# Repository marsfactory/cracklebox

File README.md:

# cracklebox
Diseño de PCB de la clasica crackle box, dandole un toque artistico al diseño. Realizado en el marco del Encuentro Federal de Grafica Tranza 2018.

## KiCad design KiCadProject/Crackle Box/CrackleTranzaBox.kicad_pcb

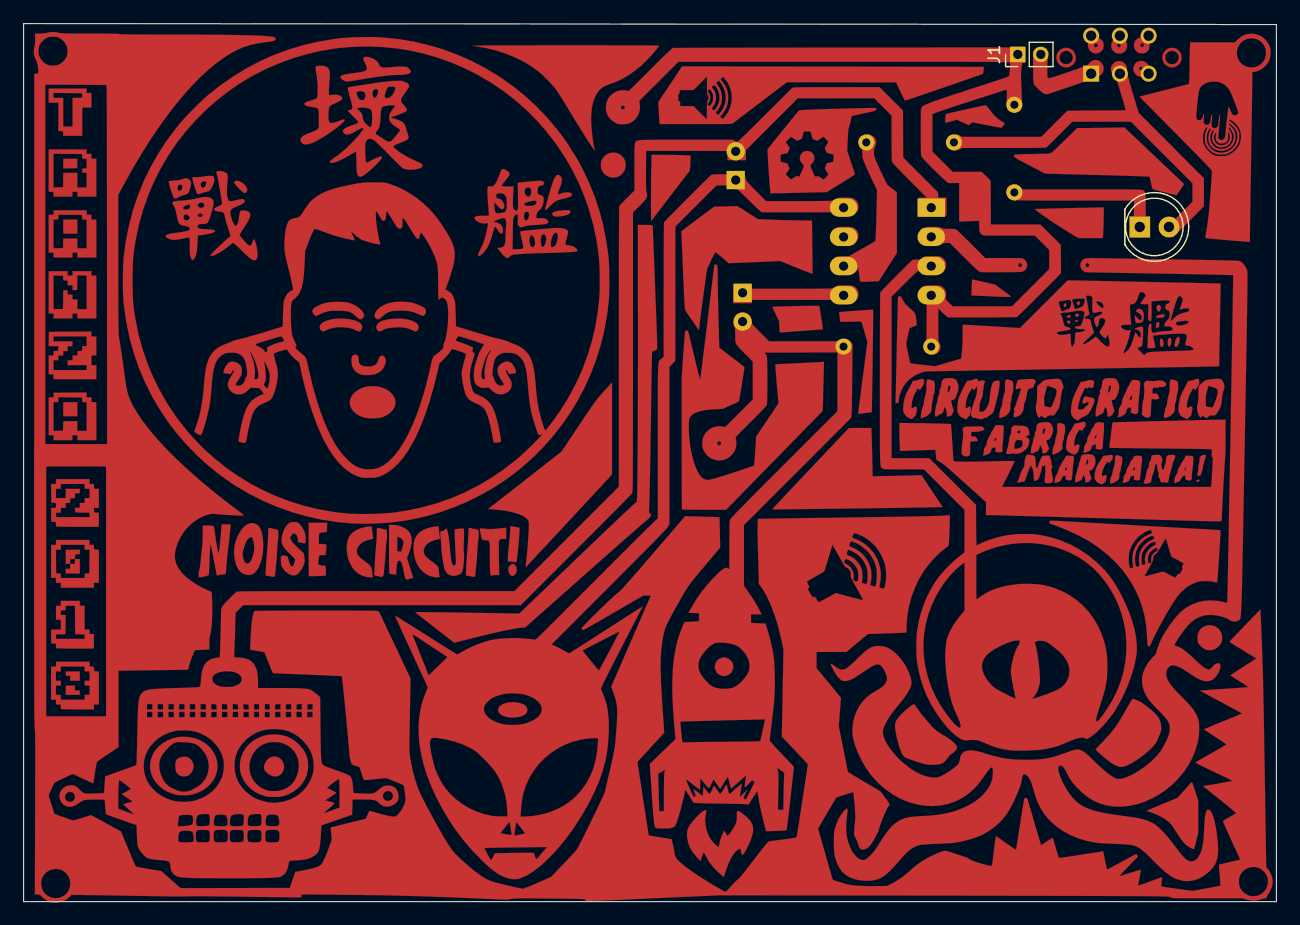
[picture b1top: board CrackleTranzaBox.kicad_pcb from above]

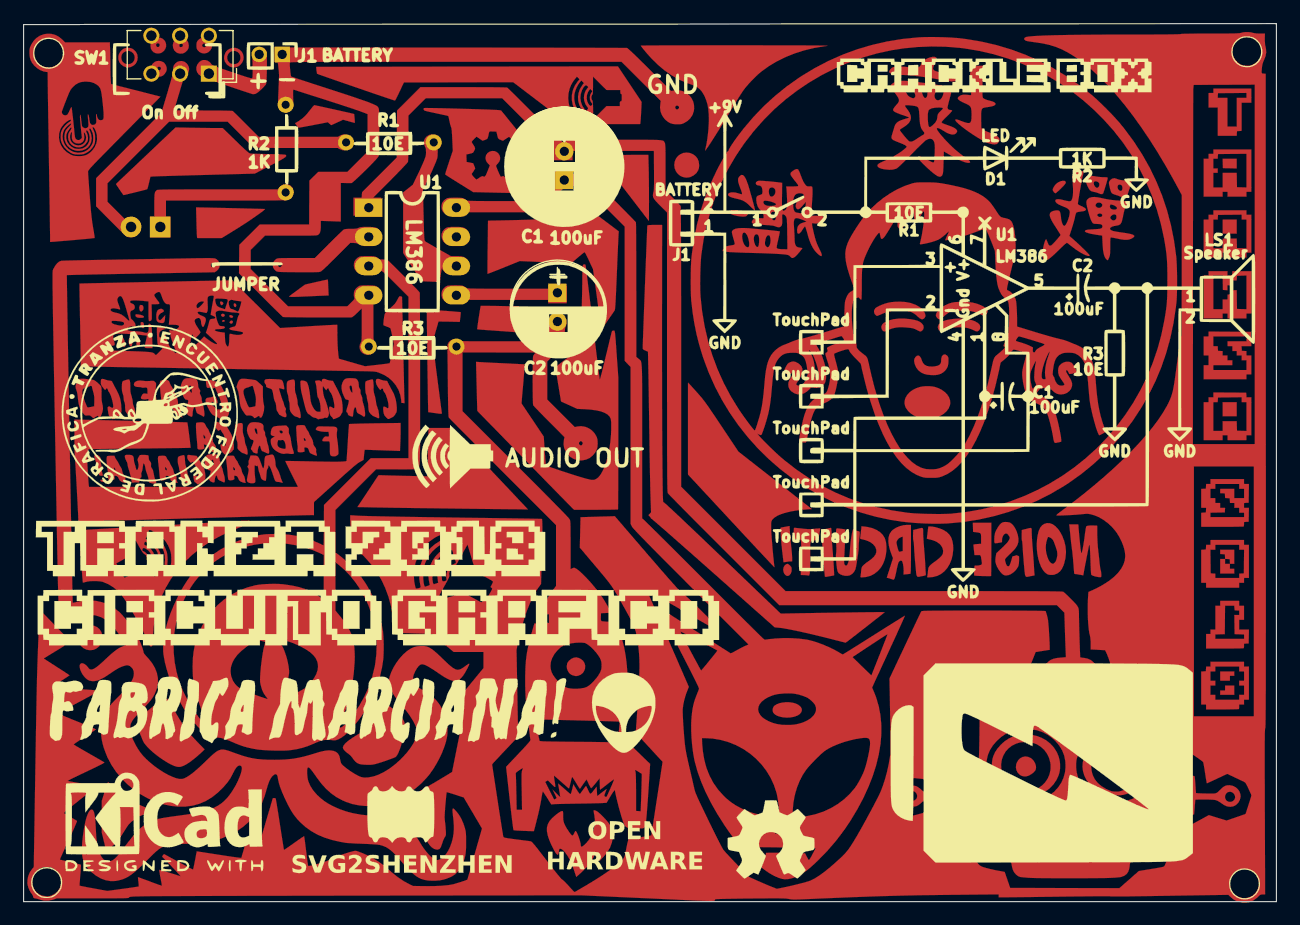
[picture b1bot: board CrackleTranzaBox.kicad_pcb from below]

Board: 2 copper layers, 108.9 x 76.3 mm, 9 parts (7 on the bottom side), 9 nets, no tracks yet.

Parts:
C1: 100uF; CP_Radial_D10.0mm_P2.50mm
C2: 100uF; CP_Radial_D8.0mm_P2.50mm
D1: LED; LED_D5.0mm
J1: BATTERY; Socket_Strip_Straight_1x02_Pitch2.00mm
R1, R3: 10E; R_Axial_DIN0204_L3.6mm_D1.6mm_P7.62mm_Horizontal
R2: 1K; R_Axial_DIN0204_L3.6mm_D1.6mm_P7.62mm_Horizontal
SW1: SW_SPST; SW_CuK_JS202011AQN_DPDT_Angled
U1: LM386; DIP-8_W7.62mm_LongPads

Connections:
+9V: J1.2, SW1.1
GND: J1.1, R2.1, R3.2, U1.4
unnamed: C1.1, U1.1
unnamed: C1.2, U1.8
unnamed: C2.1, U1.5
unnamed: C2.2, R3.1
unnamed: D1.1, R2.2
unnamed: D1.2, R1.2, SW1.2
unnamed: R1.1, U1.6
